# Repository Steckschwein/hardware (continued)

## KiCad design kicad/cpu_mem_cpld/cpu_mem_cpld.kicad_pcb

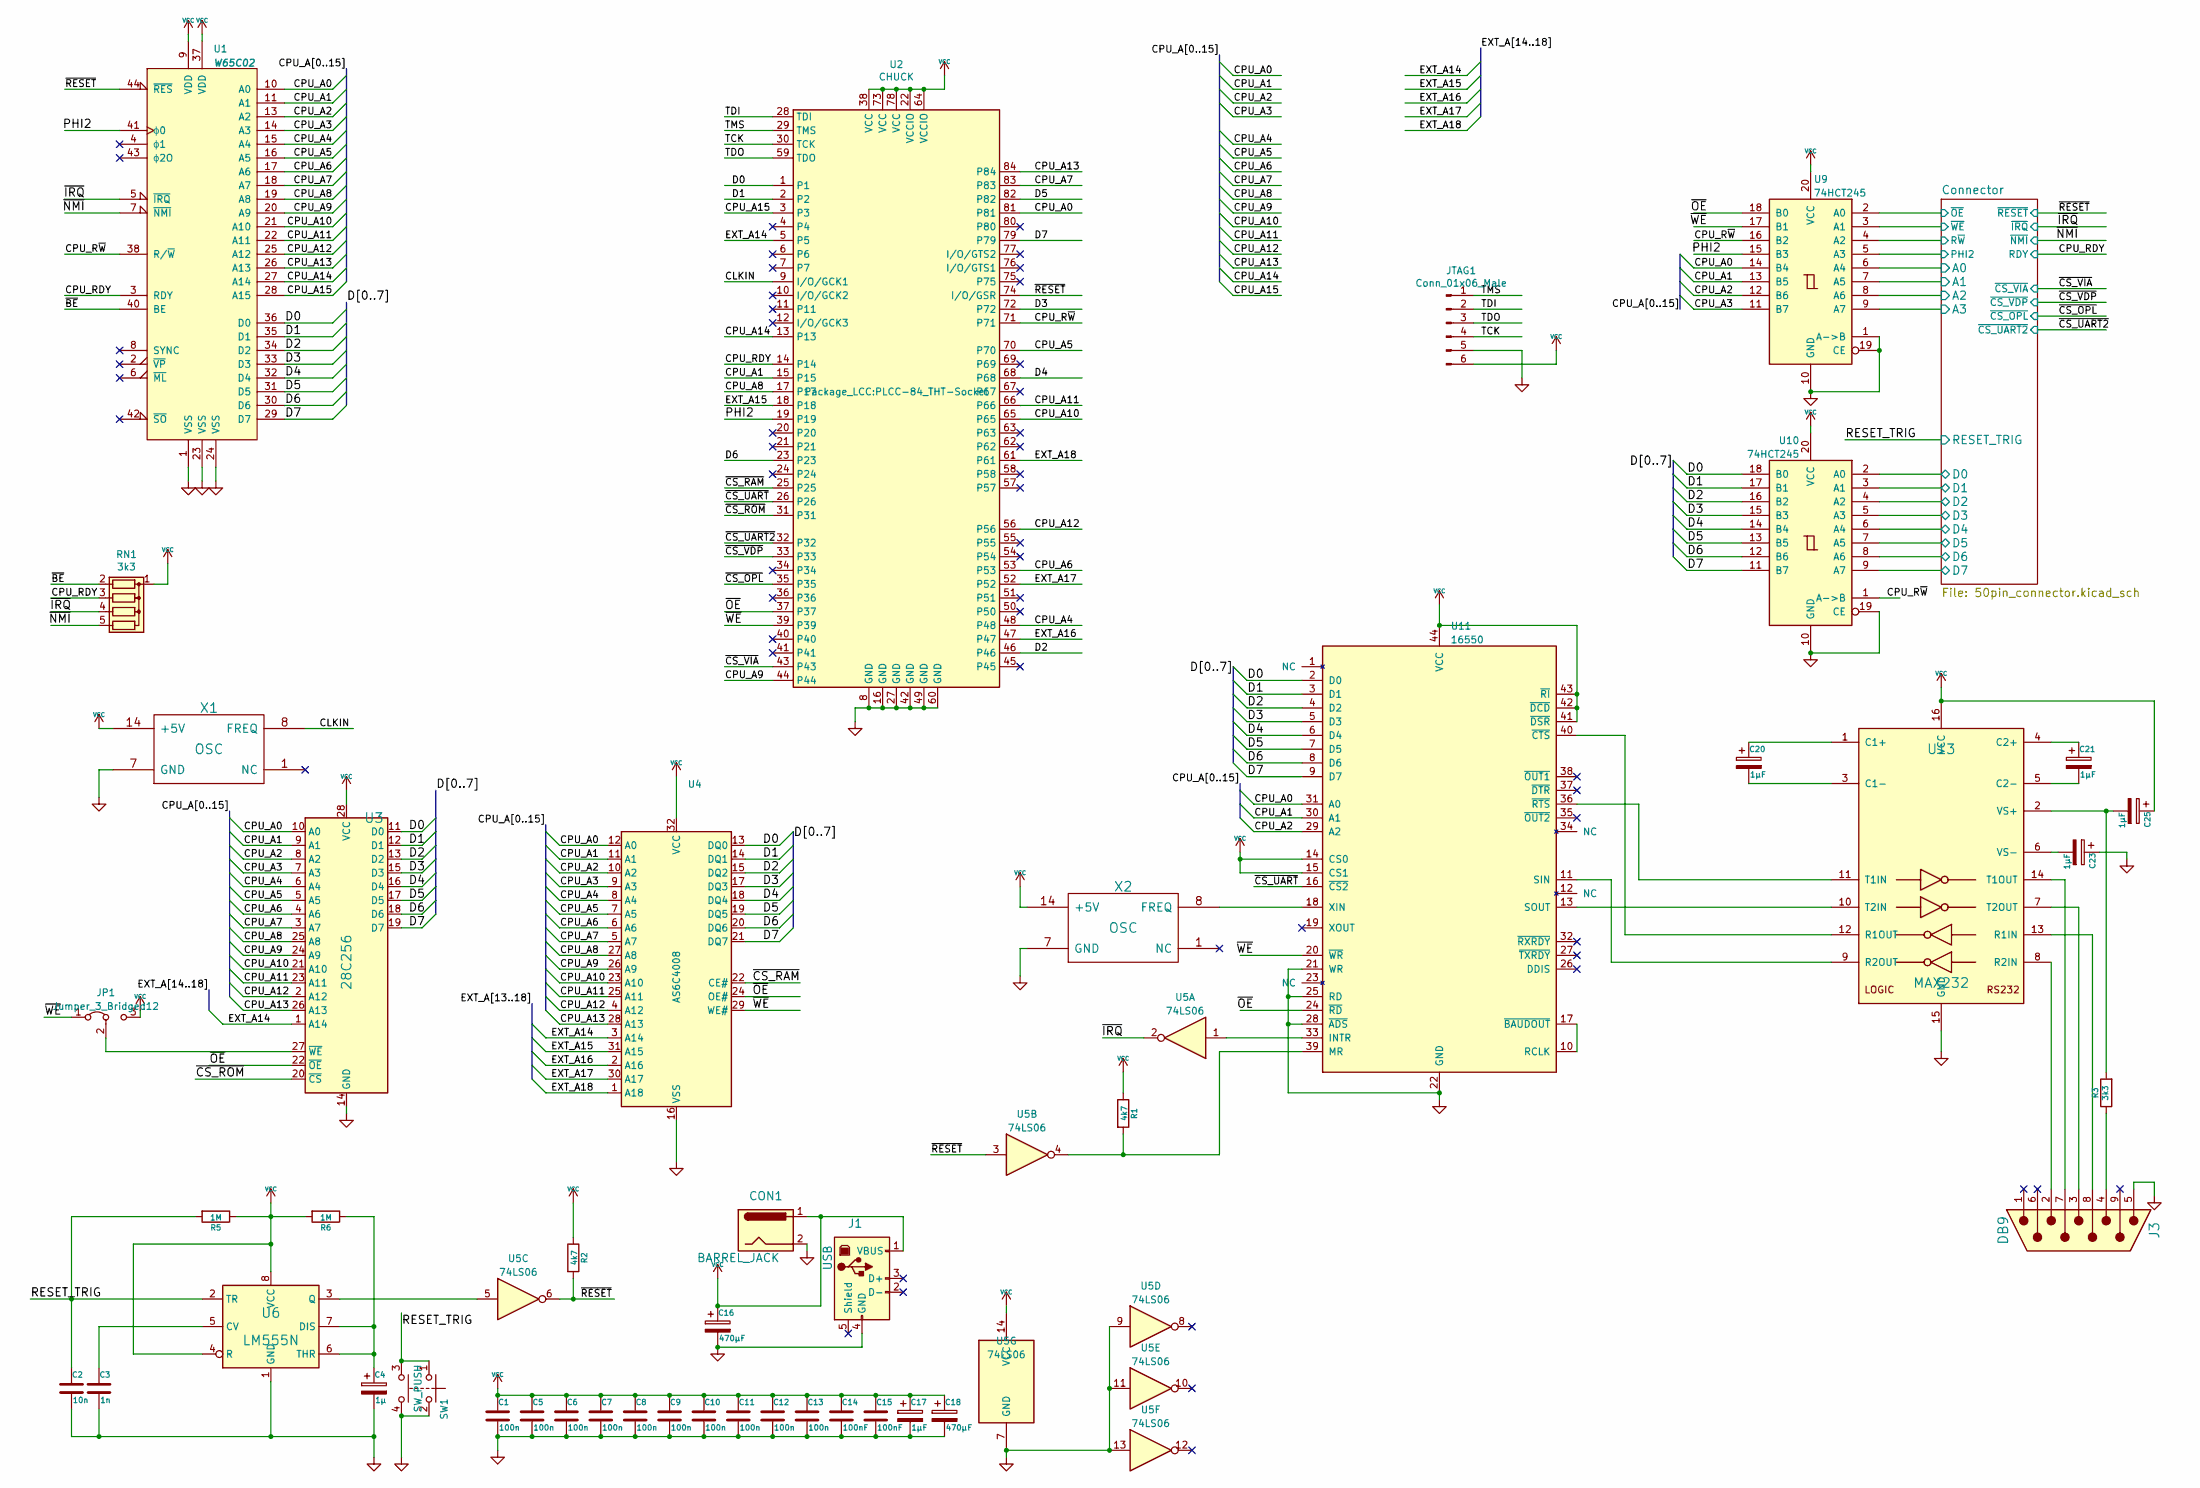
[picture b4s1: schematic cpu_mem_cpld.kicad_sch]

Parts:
C1, C5, C6, C7, C8, C9, C10, C11, C12, C13: 100n; C_1206_3216Metric_Pad1.33x1.80mm_HandSolder
C2: 10n; C_Disc_D3.0mm_W2.0mm_P2.50mm
C3: 1n; C_Disc_D3.0mm_W2.0mm_P2.50mm
C4: 1µ; CP_Radial_D4.0mm_P2.00mm
C14, C15: 100nF; C_1206_3216Metric_Pad1.33x1.80mm_HandSolder
C16, C18: 470µF; CP_Radial_D10.0mm_P5.00mm
C17, C20, C21, C23, C25: 1µF; CP_Radial_D4.0mm_P2.00mm
CON1: BARREL_JACK; BarrelJack_Horizontal
J1: USB; USB_A_Molex_67643_Horizontal
J3: DB9; DSUB-9_Male_Horizontal_P2.77x2.84mm_EdgePinOffset4.94mm_Hou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
JP1: Jumper_3_Bridged12; PinHeader_1x03_P2.54mm_Vertical
JTAG1: Conn_01x06_Male; PinHeader_1x06_P2.54mm_Vertical
R1, R2: 4k7; R_Axial_DIN0204_L3.6mm_D1.6mm_P5.08mm_Horizontal
R3: 3k3; R_Axial_DIN0204_L3.6mm_D1.6mm_P5.08mm_Horizontal
R5, R6: 1M; R_Axial_DIN0204_L3.6mm_D1.6mm_P5.08mm_Horizontal
RN1: 3k3; R_Array_SIP5
SW1: SW_PUSH; Push_E-Switch_KS01Q01
U1: W65C02; PLCC-44_THT-Socket
U2: CHUCK; PLCC-84_THT-Socket
U3: 28C256; DIP-28_W15.24mm_Socket_LongPads
U4: AS6C4008; DIP-32_W15.24mm_LongPads
U5: 74LS06; DIP-14_W7.62mm_LongPads
U6: LM555N; DIP-8_W7.62mm
U9, U10: 74HCT245; DIP-20_W7.62mm_LongPads
U11: 16550; PLCC-44_THT-Socket
U13: MAX232; DIP-16_W7.62mm_LongPads
X1, X2: OSC; Oscillator_DIP-14_LargePads

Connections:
/CLKIN: U2.9 (I/O/GCK1), X1.8 (FREQ)
/CPU_A0: U1.10 (A0), U2.81, U3.10 (A0), U4.12 (A0), U9.14 (B4), U11.31 (A0)
/CPU_A1: U1.11 (A1), U2.15, U3.9 (A1), U4.11 (A1), U9.13 (B5), U11.30 (A1)
/CPU_A2: U1.13 (A2), U3.8 (A2), U4.10 (A2), U9.12 (B6), U11.29 (A2)
/CPU_A3: U1.14 (A3), U3.7 (A3), U4.9 (A3), U9.11 (B7)
/CPU_A4: U1.15 (A4), U2.48, U3.6 (A4), U4.8 (A4)
/CPU_A5: U1.16 (A5), U2.70, U3.5 (A5), U4.7 (A5)
/CPU_A6: U1.17 (A6), U2.53, U3.4 (A6), U4.6 (A6)
/CPU_A7: U1.18 (A7), U2.83, U3.3 (A7), U4.5 (A7)
/CPU_A8: U1.19 (A8), U2.17, U3.25 (A8), U4.27 (A8)
/CPU_A9: U1.20 (A9), U2.44, U3.24 (A9), U4.26 (A9)
/CPU_A10: U1.21 (A10), U2.65, U3.21 (A10), U4.23 (A10)
/CPU_A11: U1.22 (A11), U2.66, U3.23 (A11), U4.25 (A11)
/CPU_A12: U1.25 (A12), U2.56, U3.2 (A12), U4.4 (A12)
/CPU_A13: U1.26 (A13), U2.84, U3.26 (A13), U4.28 (A13)
/CPU_A14: U1.27 (A14), U2.13
/CPU_A15: U1.28 (A15), U2.3
/CPU_RDY: RN1.3 (R2), U1.3 (RDY), U2.14; also elsewhere on the board
/CPU_R~W: U1.38 (R/~W), U2.71, U9.16 (B2), U10.1 (A->B)
/Connector/A0: U9.6 (A4); also elsewhere on the board
/Connector/A1: U9.7 (A5); also elsewhere on the board
/Connector/A2: U9.8 (A6); also elsewhere on the board
/Connector/A3: U9.9 (A7); also elsewhere on the board
/Connector/D0: U10.2 (A0); also elsewhere on the board
/Connector/D1: U10.3 (A1); also elsewhere on the board
/Connector/D2: U10.4 (A2); also elsewhere on the board
/Connector/D3: U10.5 (A3); also elsewhere on the board
/Connector/D4: U10.6 (A4); also elsewhere on the board
/Connector/D5: U10.7 (A5); also elsewhere on the board
/Connector/D6: U10.8 (A6); also elsewhere on the board
/Connector/D7: U10.9 (A7); also elsewhere on the board
/Connector/PHI2: U9.5 (A3); also elsewhere on the board
/Connector/R~W: U9.4 (A2); also elsewhere on the board
/Connector/~OE: U9.2 (A0); also elsewhere on the board
/Connector/~WE: U9.3 (A1); also elsewhere on the board
/D0: U1.36 (D0), U2.1, U3.11 (D0), U4.13 (DQ0), U10.18 (B0), U11.2 (D0)
/D1: U1.35 (D1), U2.2, U3.12 (D1), U4.14 (DQ1), U10.17 (B1), U11.3 (D1)
/D2: U1.34 (D2), U2.46, U3.13 (D2), U4.15 (DQ2), U10.16 (B2), U11.4 (D2)
/D3: U1.33 (D3), U2.72, U3.15 (D3), U4.17 (DQ3), U10.15 (B3), U11.5 (D3)
/D4: U1.32 (D4), U2.68, U3.16 (D4), U4.18 (DQ4), U10.14 (B4), U11.6 (D4)
/D5: U1.31 (D5), U2.82, U3.17 (D5), U4.19 (DQ5), U10.13 (B5), U11.7 (D5)
/D6: U1.30 (D6), U2.23, U3.18 (D6), U4.20 (DQ6), U10.12 (B6), U11.8 (D6)
/D7: U1.29 (D7), U2.79, U3.19 (D7), U4.21 (DQ7), U10.11 (B7), U11.9 (D7)
/EXT_A14: U2.5, U3.1 (A14), U4.3 (A14)
/EXT_A15: U2.18, U4.31 (A15)
/EXT_A16: U2.47, U4.2 (A16)
/EXT_A17: U2.52, U4.30 (A17)
/EXT_A18: U2.61, U4.1 (A18)
/PHI2: U1.41 (ϕ0), U2.19, U9.15 (B3)
/RESET_TRIG: C2.1, R5.2, SW1.1, SW1.3, U6.2 (TR); also elsewhere on the board
/TCK: JTAG1.4, U2.30 (TCK)
/TDI: JTAG1.2, U2.28 (TDI)
/TDO: JTAG1.3, U2.59 (TDO)
/TMS: JTAG1.1, U2.29 (TMS)
/~BE: RN1.2 (R1), U1.40 (BE)
/~CS_OPL: U2.35; also elsewhere on the board
/~CS_RAM: U2.25, U4.22 (CE#)
/~CS_ROM: U2.31, U3.20 (~CS)
/~CS_UART2: U2.32; also elsewhere on the board
/~CS_UART: U2.26, U11.16 (~CS2)
/~CS_VDP: U2.33; also elsewhere on the board
/~CS_VIA: U2.43; also elsewhere on the board
/~IRQ: RN1.4 (R3), U1.5 (~IRQ), U5.2; also elsewhere on the board
/~NMI: RN1.5 (R4), U1.7 (~NMI); also elsewhere on the board
/~OE: U2.37, U3.22 (~OE), U4.24 (OE#), U9.18 (B0), U11.24 (~RD)
/~RESET: R2.2, U1.44 (~RES), U2.74 (I/O/GSR), U5.3, U5.6; also elsewhere on the board
/~WE: JP1.1 (A), U2.39, U4.29 (WE#), U9.17 (B1), U11.20 (~WR)
GND: C1.2, C2.2, C3.2, C4.2, C5.2, C6.2, C7.2, C8.2, C9.2, C10.2, C11.2, C12.2, C13.2, C14.2, C15.2, C16.2, C17.2, C18.2, C23.1, CON1.2, J1.4 (GND), J3.5, JTAG1.5, SW1.2, SW1.4, U1.1 (VSS), U1.23 (VSS), U1.24 (VSS), U2.8 (GND), U2.16 (GND), U2.27 (GND), U2.42 (GND), U2.49 (GND), U2.60 (GND), U3.14 (GND), U4.16 (VSS), U5.7 (GND), U5.9, U5.11, U5.13, U6.1 (GND), U9.1 (A->B), U9.10 (GND), U9.19 (CE), U10.10 (GND), U10.19 (CE), U11.21 (WR), U11.22 (GND), U11.25 (RD), U11.28 (~ADS), U13.15 (GND), X1.7 (GND), X2.7 (GND); also elsewhere on the board
unnamed: C3.1, U6.5 (CV)
unnamed: C4.1, R6.1, U6.6 (THR), U6.7 (DIS)
unnamed: C20.1, U13.1 (C1+)
unnamed: C20.2, U13.3 (C1-)
unnamed: C21.1, U13.4 (C2+)
unnamed: C21.2, U13.5 (C2-)
unnamed: C23.2, U13.6 (VS-)
unnamed: C25.2, R3.2, U13.2 (VS+)
unnamed: J3.2, U13.8 (R2IN)
unnamed: J3.3, U13.7 (T2OUT)
unnamed: J3.4, R3.1
unnamed: J3.7, U13.14 (T1OUT)
unnamed: J3.8, U13.13 (R1IN)
unnamed: JP1.2 (C), U3.27 (~WE)
unnamed: R1.2, U5.4, U11.39 (MR)
unnamed: U5.5, U6.3 (Q)
unnamed: U11.10 (RCLK), U11.17 (~BAUDOUT)
unnamed: U11.11 (SIN), U13.9 (R2OUT)
unnamed: U11.13 (SOUT), U13.10 (T2IN)
unnamed: U11.18 (XIN), X2.8 (FREQ)
unnamed: U5.1, U11.33 (INTR)
unnamed: U11.36 (~RTS), U13.11 (T1IN)
unnamed: U11.40 (~CTS), U13.12 (R1OUT)
VCC: C1.1, C5.1, C6.1, C7.1, C8.1, C9.1, C10.1, C11.1, C12.1, C13.1, C14.1, C15.1, C16.1, C17.1, C18.1, C25.1, CON1.1, J1.1 (VBUS), JP1.3 (B), JTAG1.6, R1.1, R2.1, R5.1, R6.2, RN1.1 (common), U1.9 (VDD), U1.37 (VDD), U2.22 (VCCIO), U2.38 (VCC), U2.64 (VCCIO), U2.73 (VCC), U2.78 (VCC), U3.28 (VCC), U4.32 (VCC), U5.14 (VCC), U6.4 (R), U6.8 (VCC), U9.20 (VCC), U10.20 (VCC), U11.14 (CS0), U11.15 (CS1), U11.41 (~DSR), U11.42 (~DCD), U11.43 (~RI), U11.44 (VCC), U13.16 (VCC), X1.14 (+5V), X2.14 (+5V); also elsewhere on the board

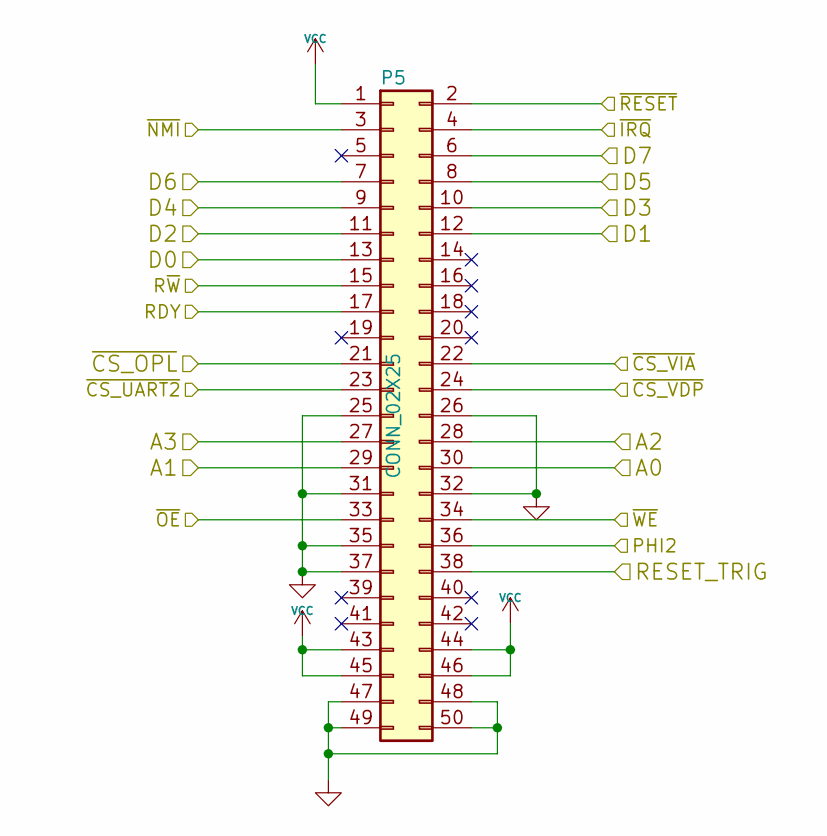
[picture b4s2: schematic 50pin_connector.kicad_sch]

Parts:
P5: CONN_02X25; PinHeader_2x25_P2.54mm_Horizontal

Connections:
/CPU_RDY: P5.17; also elsewhere on the board
/Connector/A0: P5.30; also elsewhere on the board
/Connector/A1: P5.29; also elsewhere on the board
/Connector/A2: P5.28; also elsewhere on the board
/Connector/A3: P5.27; also elsewhere on the board
/Connector/D0: P5.13; also elsewhere on the board
/Connector/D1: P5.12; also elsewhere on the board
/Connector/D2: P5.11; also elsewhere on the board
/Connector/D3: P5.10; also elsewhere on the board
/Connector/D4: P5.9; also elsewhere on the board
/Connector/D5: P5.8; also elsewhere on the board
/Connector/D6: P5.7; also elsewhere on the board
/Connector/D7: P5.6; also elsewhere on the board
/Connector/PHI2: P5.36; also elsewhere on the board
/Connector/R~W: P5.15; also elsewhere on the board
/Connector/~OE: P5.33; also elsewhere on the board
/Connector/~WE: P5.34; also elsewhere on the board
/RESET_TRIG: P5.38; also elsewhere on the board
/~CS_OPL: P5.21; also elsewhere on the board
/~CS_UART2: P5.23; also elsewhere on the board
/~CS_VDP: P5.24; also elsewhere on the board
/~CS_VIA: P5.22; also elsewhere on the board
/~IRQ: P5.4; also elsewhere on the board
/~NMI: P5.3; also elsewhere on the board
/~RESET: P5.2; also elsewhere on the board
GND: P5.25, P5.26, P5.31, P5.32, P5.35, P5.37, P5.47, P5.48, P5.49, P5.50; also elsewhere on the board
VCC: P5.1, P5.43, P5.44, P5.45, P5.46; also elsewhere on the board

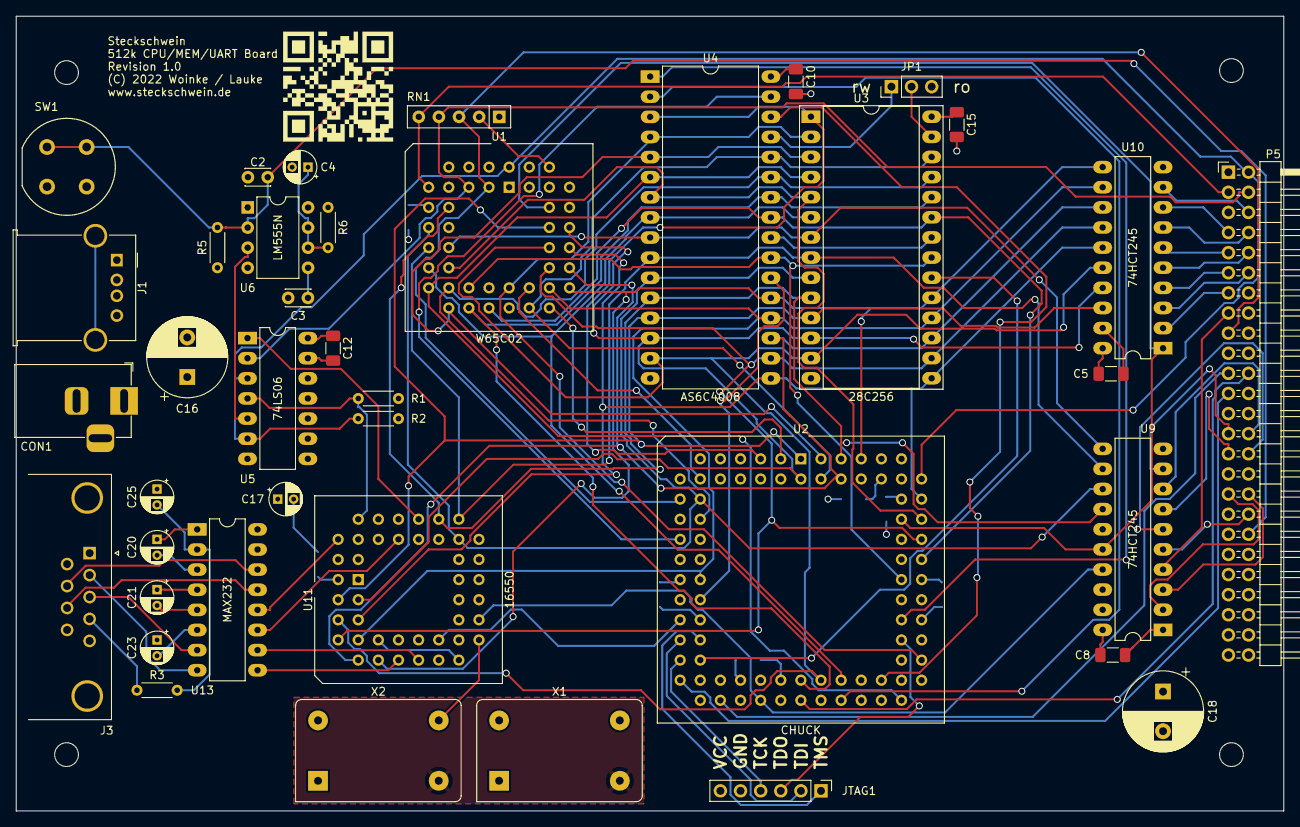
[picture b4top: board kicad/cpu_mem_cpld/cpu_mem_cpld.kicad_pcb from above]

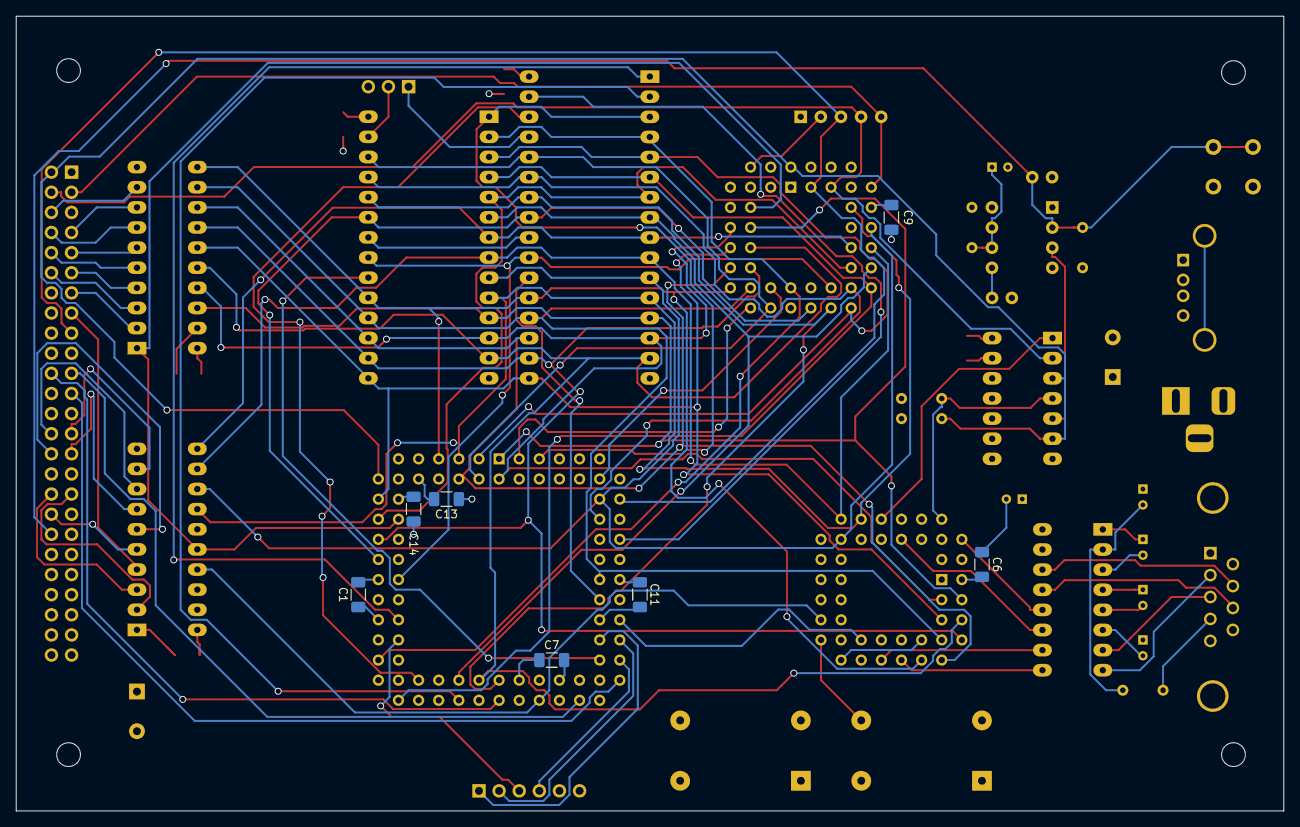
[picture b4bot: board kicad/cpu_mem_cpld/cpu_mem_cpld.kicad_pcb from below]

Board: 4 copper layers, 160.0 x 100.3 mm, 51 parts (7 on the bottom side), 92 nets.

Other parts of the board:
MH1, MH2, MH3, MH4: MountingHole_3mm_RevA_Date21Jun2010; MountingHole_3mm

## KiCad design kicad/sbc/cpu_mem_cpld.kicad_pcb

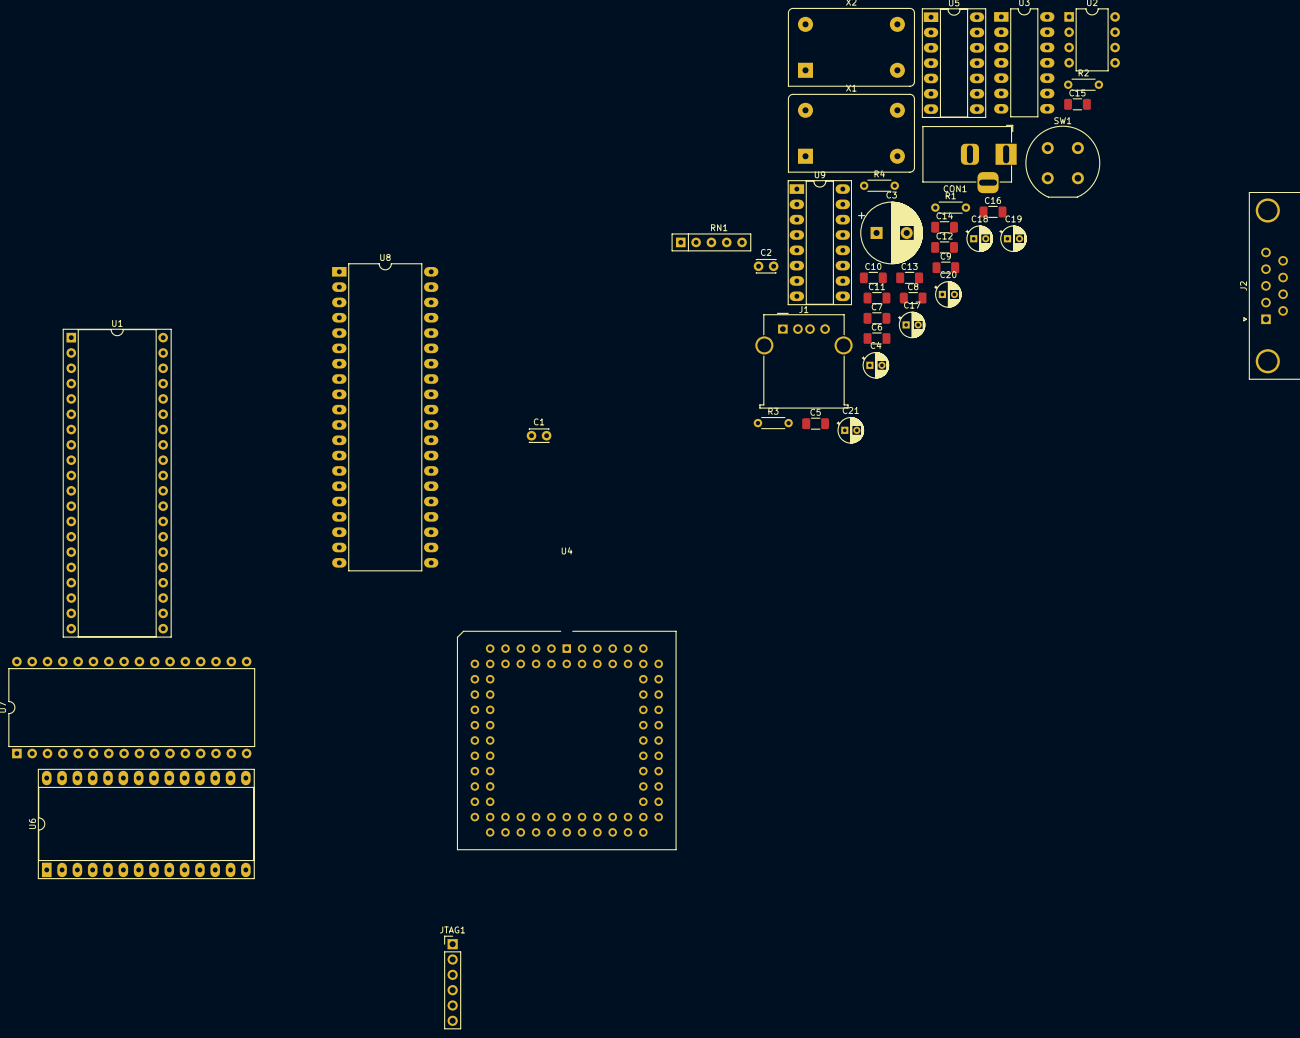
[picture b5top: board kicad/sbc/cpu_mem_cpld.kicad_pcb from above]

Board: 4 copper layers, 42 parts (0 on the bottom side), 72 nets, no tracks yet.

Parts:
C1: 10n; C_Disc_D3.0mm_W2.0mm_P2.50mm
C2: 1n; C_Disc_D3.0mm_W2.0mm_P2.50mm
C3: 470µF; CP_Radial_D10.0mm_P5.00mm
C4: 1µ; CP_Radial_D4.0mm_P2.00mm
C5, C6, C7, C8, C9, C10, C11, C12, C13, C14: 100n; C_1206_3216Metric_Pad1.33x1.80mm_HandSolder
C15, C16: 100nF; C_1206_3216Metric_Pad1.33x1.80mm_HandSolder
C17, C18, C19, C20, C21: 1µF; CP_Radial_D4.0mm_P2.00mm
CON1: BARREL_JACK; BarrelJack_Horizontal
J1: USB; USB_A_Molex_67643_Horizontal
J2: DB9; DSUB-9_Male_Horizontal_P2.77x2.84mm_EdgePinOffset4.94mm_Hou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
JTAG1: Conn_01x06_Male; PinHeader_1x06_P2.54mm_Vertical
R1, R2: 1M; R_Axial_DIN0204_L3.6mm_D1.6mm_P5.08mm_Horizontal
R3: 4k7; R_Axial_DIN0204_L3.6mm_D1.6mm_P5.08mm_Horizontal
R4: 3k3; R_Axial_DIN0204_L3.6mm_D1.6mm_P5.08mm_Horizontal
RN1: R_Network04; R_Array_SIP5
SW1: SW_PUSH; Push_E-Switch_KS01Q01
U1: 65C02; DIP-40_W15.24mm_Socket
U2: LM555N; DIP-8_W7.62mm
U3: 74HCT00; DIP-14_W7.62mm_LongPads
U4: XC95108PC84; PLCC-84_THT-Socket
U5: 74LS06; DIP-14_W7.62mm_Socket_LongPads
U6: 28C256; DIP-28_W15.24mm_Socket_LongPads
U7: AS6C4008-55PCN; DIP-32_W15.24mm
U8: 16550; DIP-40_W15.24mm_LongPads
U9: MAX232; DIP-16_W7.62mm_Socket_LongPads
X1, X2: OSC; Oscillator_DIP-14_LargePads

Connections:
/CLKIN: U4.9, X1.8
/CPU_A0: U1.9, U4.24, U6.10, U7.12, U8.28
/CPU_A1: U1.10, U4.25, U6.9, U7.11, U8.27
/CPU_A2: U1.11, U4.26, U6.8, U7.10, U8.26
/CPU_A3: U1.12, U4.31, U6.7, U7.9
/CPU_A4: U1.13, U4.32, U6.6, U7.8
/CPU_A5: U1.14, U4.33, U6.5, U7.7
/CPU_A6: U1.15, U4.34, U6.4, U7.6
/CPU_A7: U1.16, U4.35, U6.3, U7.5
/CPU_A8: U1.17, U4.36, U6.25, U7.27
/CPU_A9: U1.18, U4.37, U6.24, U7.26
/CPU_A10: U1.19, U4.39, U6.21, U7.23
/CPU_A11: U1.20, U4.40, U6.23, U7.25
/CPU_A12: U1.22, U4.41, U6.2, U7.4
/CPU_A13: U1.23, U4.43
/CPU_A14: U1.24, U4.44
/CPU_A15: U1.25, U4.45
/D0: U1.33, U4.1, U6.11, U7.13, U8.1
/D1: U1.32, U4.2, U6.12, U7.14, U8.2
/D2: U1.31, U4.3, U6.13, U7.15, U8.3
/D3: U1.30, U4.4, U6.15, U7.17, U8.4
/D4: U1.29, U4.5, U6.16, U7.18, U8.5
/D5: U1.28, U4.6, U6.17, U7.19, U8.6
/D6: U1.27, U4.7, U6.18, U7.20, U8.7
/D7: U1.26, U4.10, U6.19, U7.21, U8.8
/EXT_A13: U4.84, U6.26, U7.28
/EXT_A14: U4.83, U6.1, U7.3
/EXT_A15: U4.82, U7.31
/EXT_A16: U4.81, U7.2
/EXT_A17: U4.80, U7.30
/EXT_A18: U4.79, U7.1
/RESET_TRIG: C1.1, R1.2, SW1.1, SW1.3, U2.2
/TCK: JTAG1.4, U4.30
/TDI: JTAG1.2, U4.28
/TDO: JTAG1.3, U4.59
/TMS: JTAG1.1, U4.29
/~BE: RN1.5, U1.36
/~CS_RAM: U4.52, U7.22
/~CS_ROM: U4.53, U6.20
/~CS_UART: U4.54, U8.14
/~RD: U4.48, U6.22, U7.24, U8.21
/~WR: U4.47, U7.29, U8.18
GND: C1.2, C2.2, C3.2, C4.2, C5.2, C6.2, C7.2, C8.2, C9.2, C10.2, C11.2, C12.2, C13.2, C14.2, C15.2, C16.2, C17.2, C20.1, CON1.2, J1.4, J2.5, JTAG1.5, SW1.2, SW1.4, U1.21, U2.1, U3.7, U4.8, U4.11, U4.12, U4.13, U4.14, U4.15, U4.16, U4.17, U4.18, U4.19, U4.20, U4.21, U4.23, U4.27, U4.42, U4.49, U4.60, U4.61, U4.62, U4.63, U4.65, U4.66, U4.67, U4.68, U4.69, U4.70, U4.71, U4.72, U4.75, U4.76, U4.77, U6.14, U7.16, U8.19, U8.20, U8.22, U8.25, U9.15, X1.7, X2.7
unnamed: C2.1, U2.5
unnamed: C4.1, R2.1, U2.6, U2.7
unnamed: C18.1, U9.1
unnamed: C18.2, U9.3
unnamed: C19.1, U9.4
unnamed: C19.2, U9.5
unnamed: C20.2, U9.6
unnamed: C21.2, R4.2, U9.2
unnamed: J2.2, U9.8
unnamed: J2.3, U9.7
unnamed: J2.4, R4.1
unnamed: J2.7, U9.14
unnamed: J2.8, U9.13
unnamed: R3.2, U5.4, U8.35
unnamed: U2.3, U3.1, U3.2
unnamed: U5.1, U8.30
unnamed: U8.10, U9.9
unnamed: U8.11, U9.10
unnamed: U8.9, U8.15
unnamed: U8.16, X2.8
unnamed: U8.32, U9.11
unnamed: U8.36, U9.12
PHI2: U1.39, U4.51
RDY: RN1.2, U1.2, U4.46
VCC: C3.1, C5.1, C6.1, C7.1, C8.1, C9.1, C10.1, C11.1, C12.1, C13.1, C14.1, C15.1, C16.1, C17.1, C21.1, CON1.1, J1.1, JTAG1.6, R1.1, R2.2, R3.1, RN1.1, U1.8, U2.4, U2.8, U3.14, U4.22, U4.38, U4.64, U4.73, U4.78, U6.27, U6.28, U7.32, U8.12, U8.13, U8.37, U8.38, U8.39, U8.40, U9.16, X1.14, X2.14
~IRQ: RN1.3, U1.4
~NMI: RN1.4, U1.6
~RESET: U1.40, U3.3, U4.74
~RW: U1.34, U4.50

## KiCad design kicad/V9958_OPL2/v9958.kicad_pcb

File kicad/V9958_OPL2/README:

This is the current version of the video/audio board integrating both the V9958 with maximum memory configuration and the 
OPL2 sound chip onto one single board, making this the "multimedia board"

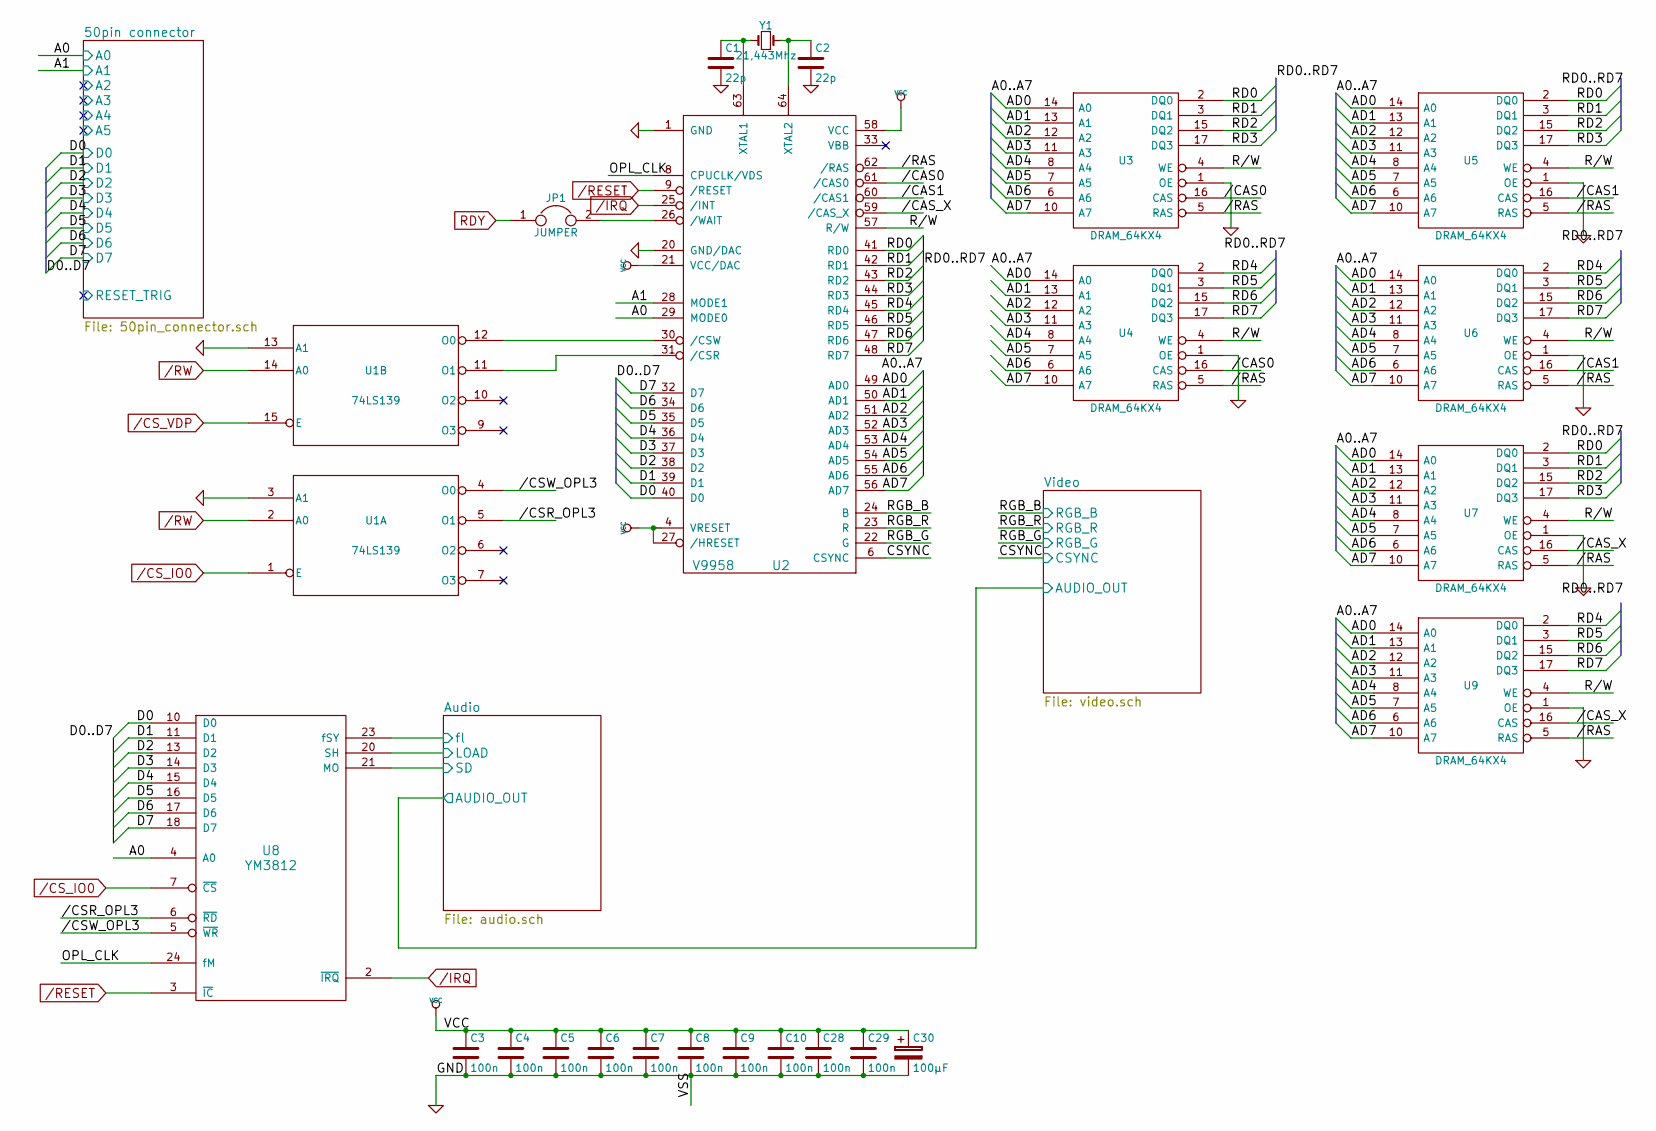
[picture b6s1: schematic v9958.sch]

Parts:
C1, C2: 22p; C_Disc_D3.0mm_W1.6mm_P2.50mm
C3, C4, C5, C6, C7, C8, C9, C10, C28, C29: 100n; C_Disc_D3.0mm_W1.6mm_P2.50mm
C30: 100µF; CP_Radial_D7.5mm_P2.50mm
JP1: JUMPER; Pin_Header_Straight_1x02_Pitch2.54mm
U1: 74LS139; DIP-16_W7.62mm_LongPads
U2: V9958; SDIP64
U3, U4, U5, U6, U7, U9: DRAM_64KX4; DIP-18_W7.62mm_LongPads
U8: YM3812; DIP-24_W15.24mm_LongPads
Y1: 21,443Mhz; Crystal_HC49-U_Vertical

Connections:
//CAS0: U2.61 (/CAS0), U3.16 (CAS), U4.16 (CAS)
//CAS1: U2.60 (/CAS1), U5.16 (CAS), U6.16 (CAS)
//CAS_X: U2.59 (/CAS_X), U7.16 (CAS), U9.16 (CAS)
//CSR_OPL3: U1.5 (O1), U8.6 (~RD)
//CSW_OPL3: U1.4 (O0), U8.5 (~WR)
//RAS: U2.62 (/RAS), U3.5 (RAS), U4.5 (RAS), U5.5 (RAS), U6.5 (RAS), U7.5 (RAS), U9.5 (RAS)
/A0: U2.29 (MODE0), U8.4 (A0); also elsewhere on the board
/A1: U2.28 (MODE1); also elsewhere on the board
/AD0: U2.49 (AD0), U3.14 (A0), U4.14 (A0), U5.14 (A0), U6.14 (A0), U7.14 (A0), U9.14 (A0)
/AD1: U2.50 (AD1), U3.13 (A1), U4.13 (A1), U5.13 (A1), U6.13 (A1), U7.13 (A1), U9.13 (A1)
/AD2: U2.51 (AD2), U3.12 (A2), U4.12 (A2), U5.12 (A2), U6.12 (A2), U7.12 (A2), U9.12 (A2)
/AD3: U2.52 (AD3), U3.11 (A3), U4.11 (A3), U5.11 (A3), U6.11 (A3), U7.11 (A3), U9.11 (A3)
/AD4: U2.53 (AD4), U3.8 (A4), U4.8 (A4), U5.8 (A4), U6.8 (A4), U7.8 (A4), U9.8 (A4)
/AD5: U2.54 (AD5), U3.7 (A5), U4.7 (A5), U5.7 (A5), U6.7 (A5), U7.7 (A5), U9.7 (A5)
/AD6: U2.55 (AD6), U3.6 (A6), U4.6 (A6), U5.6 (A6), U6.6 (A6), U7.6 (A6), U9.6 (A6)
/AD7: U2.56 (AD7), U3.10 (A7), U4.10 (A7), U5.10 (A7), U6.10 (A7), U7.10 (A7), U9.10 (A7)
/Audio/LOAD: U8.20 (SH); also elsewhere on the board
/Audio/SD: U8.21 (MO); also elsewhere on the board
/Audio/fl: U8.23 (fSY); also elsewhere on the board
/CSYNC: U2.6 (CSYNC); also elsewhere on the board
/CS_IO0: U1.1 (E), U8.7 (~CS); also elsewhere on the board
/CS_VDP: U1.15 (E); also elsewhere on the board
/D0: U2.40 (D0), U8.10 (D0); also elsewhere on the board
/D1: U2.39 (D1), U8.11 (D1); also elsewhere on the board
/D2: U2.38 (D2), U8.13 (D2); also elsewhere on the board
/D3: U2.37 (D3), U8.14 (D3); also elsewhere on the board
/D4: U2.36 (D4), U8.15 (D4); also elsewhere on the board
/D5: U2.35 (D5), U8.16 (D5); also elsewhere on the board
/D6: U2.34 (D6), U8.17 (D6); also elsewhere on the board
/D7: U2.32 (D7), U8.18 (D7); also elsewhere on the board
/IRQ: U2.25 (/INT), U8.2 (~IRQ); also elsewhere on the board
/OPL_CLK: U2.8 (CPUCLK/VDS), U8.24 (fM)
/R/W: U2.57 (R/W), U3.4 (WE), U4.4 (WE), U5.4 (WE), U6.4 (WE), U7.4 (WE), U9.4 (WE)
/RD0: U2.41 (RD0), U3.2 (DQ0), U5.2 (DQ0), U7.2 (DQ0)
/RD1: U2.42 (RD1), U3.3 (DQ1), U5.3 (DQ1), U7.3 (DQ1)
/RD2: U2.43 (RD2), U3.15 (DQ2), U5.15 (DQ2), U7.15 (DQ2)
/RD3: U2.44 (RD3), U3.17 (DQ3), U5.17 (DQ3), U7.17 (DQ3)
/RD4: U2.45 (RD4), U4.2 (DQ0), U6.2 (DQ0), U9.2 (DQ0)
/RD5: U2.46 (RD5), U4.3 (DQ1), U6.3 (DQ1), U9.3 (DQ1)
/RD6: U2.47 (RD6), U4.15 (DQ2), U6.15 (DQ2), U9.15 (DQ2)
/RD7: U2.48 (RD7), U4.17 (DQ3), U6.17 (DQ3), U9.17 (DQ3)
/RESET: U2.9 (/RESET), U8.3 (~IC); also elsewhere on the board
/RGB_B: U2.24 (B); also elsewhere on the board
/RGB_G: U2.22 (G); also elsewhere on the board
/RGB_R: U2.23 (R); also elsewhere on the board
/RW: U1.2 (A0), U1.14 (A0); also elsewhere on the board
GND: C1.2, C2.2, C3.2, C4.2, C5.2, C6.2, C7.2, C8.2, C9.2, C10.2, C28.2, C29.2, C30.2, U1.3 (A1), U1.8 (GND), U1.13 (A1), U2.1 (GND), U2.20 (GND/DAC), U3.1 (OE), U3.18 (VSS), U4.1 (OE), U4.18 (VSS), U5.1 (OE), U5.18 (VSS), U6.1 (OE), U6.18 (VSS), U7.1 (OE), U7.18 (VSS), U8.12 (GND), U9.1 (OE), U9.18 (VSS); also elsewhere on the board
unnamed: C1.1, U2.63 (XTAL1), Y1.1
unnamed: C2.1, U2.64 (XTAL2), Y1.2
unnamed: JP1.2, U2.26 (/WAIT)
unnamed: U1.11 (O1), U2.31 (/CSR)
unnamed: U1.12 (O0), U2.30 (/CSW)
RDY: JP1.1; also elsewhere on the board
VCC: C3.1, C4.1, C5.1, C6.1, C7.1, C8.1, C9.1, C10.1, C28.1, C29.1, C30.1, U1.16 (VCC), U2.4 (VRESET), U2.21 (VCC/DAC), U2.27 (/HRESET), U2.58 (VCC), U3.9 (VCC), U4.9 (VCC), U5.9 (VCC), U6.9 (VCC), U7.9 (VCC), U8.1 (VCC), U9.9 (VCC); also elsewhere on the board

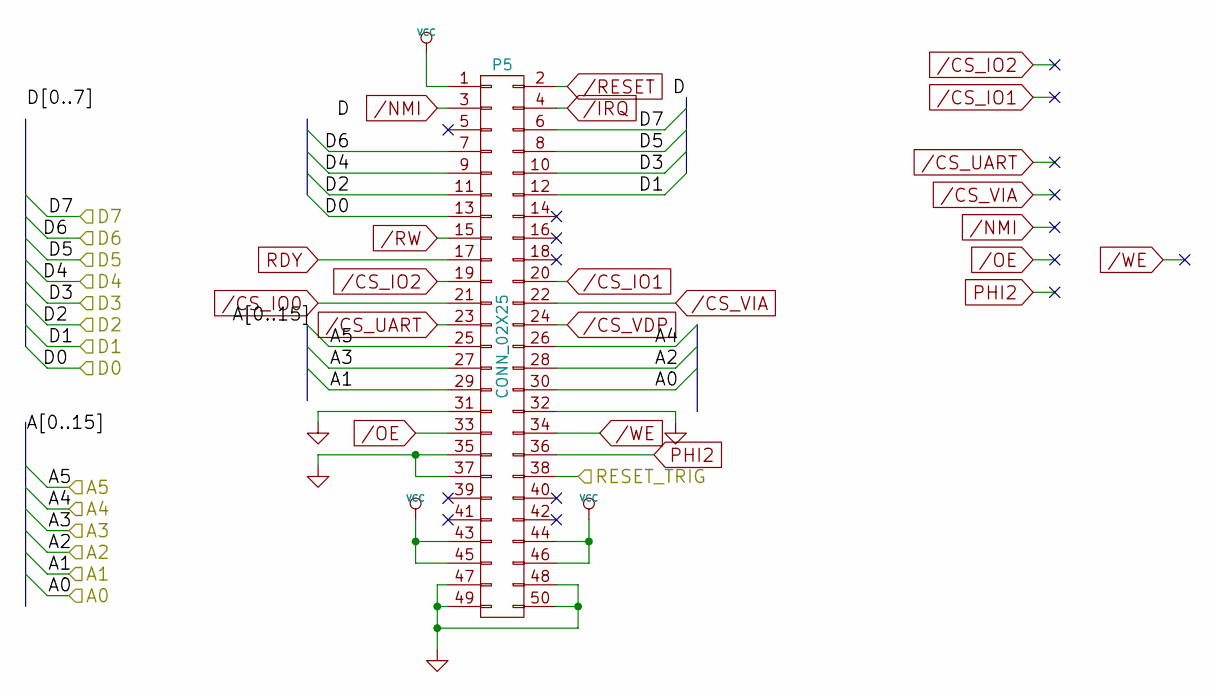
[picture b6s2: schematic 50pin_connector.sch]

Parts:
P5: CONN_02X25; Pin_Header_Angled_2x25

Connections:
/50pin connector/A2: P5.28
/50pin connector/A3: P5.27
/50pin connector/A4: P5.26
/50pin connector/A5: P5.25
/50pin connector/RESET_TRIG: P5.38
/A0: P5.30; also elsewhere on the board
/A1: P5.29; also elsewhere on the board
/CS_IO0: P5.21; also elsewhere on the board
/CS_IO1: P5.20
/CS_IO2: P5.19
/CS_UART: P5.23
/CS_VDP: P5.24; also elsewhere on the board
/CS_VIA: P5.22
/D0: P5.13; also elsewhere on the board
/D1: P5.12; also elsewhere on the board
/D2: P5.11; also elsewhere on the board
/D3: P5.10; also elsewhere on the board
/D4: P5.9; also elsewhere on the board
/D5: P5.8; also elsewhere on the board
/D6: P5.7; also elsewhere on the board
/D7: P5.6; also elsewhere on the board
/IRQ: P5.4; also elsewhere on the board
/NMI: P5.3
/OE: P5.33
/RESET: P5.2; also elsewhere on the board
/RW: P5.15; also elsewhere on the board
/WE: P5.34
GND: P5.31, P5.32, P5.35, P5.37, P5.47, P5.48, P5.49, P5.50; also elsewhere on the board
PHI2: P5.36
RDY: P5.17; also elsewhere on the board
VCC: P5.1, P5.43, P5.44, P5.45, P5.46; also elsewhere on the board
